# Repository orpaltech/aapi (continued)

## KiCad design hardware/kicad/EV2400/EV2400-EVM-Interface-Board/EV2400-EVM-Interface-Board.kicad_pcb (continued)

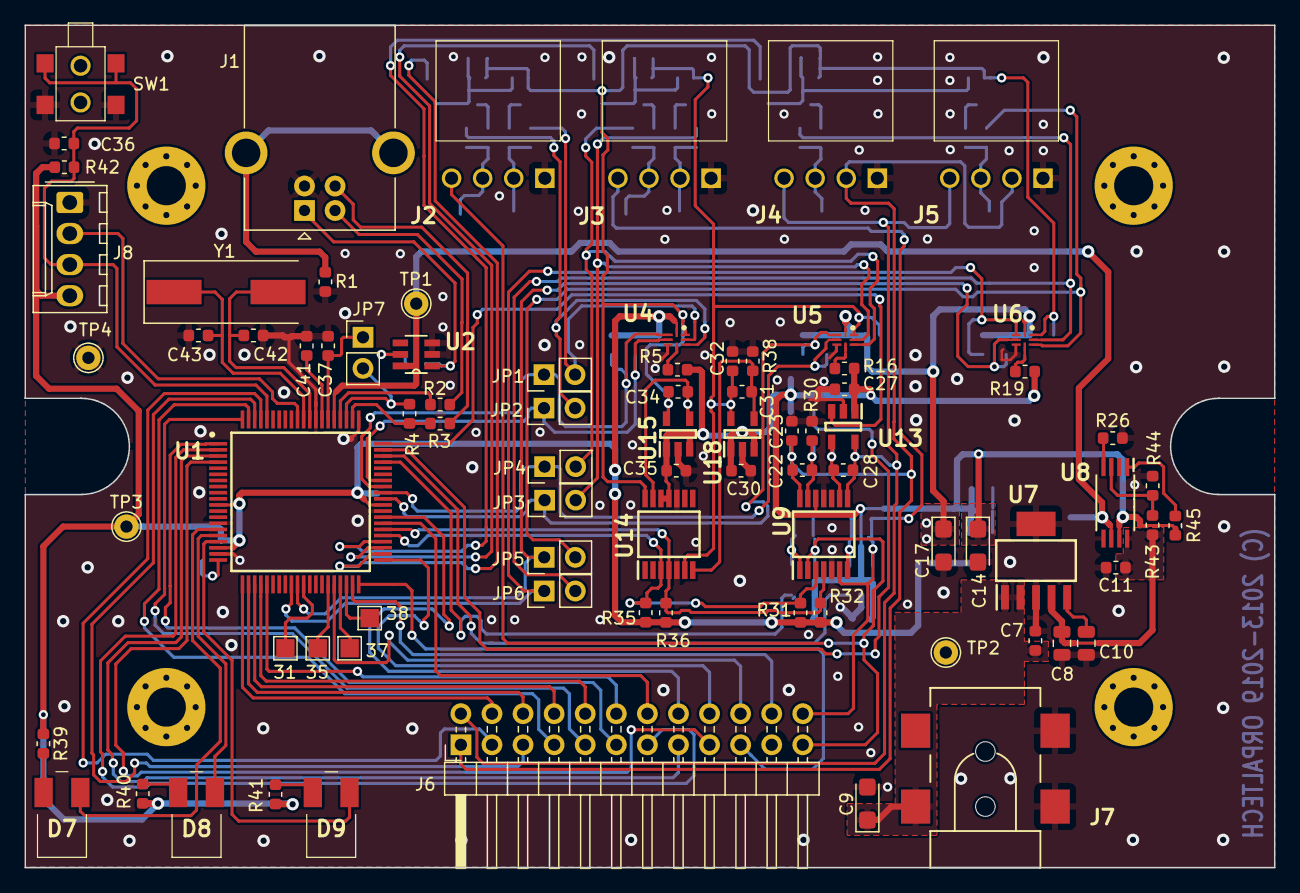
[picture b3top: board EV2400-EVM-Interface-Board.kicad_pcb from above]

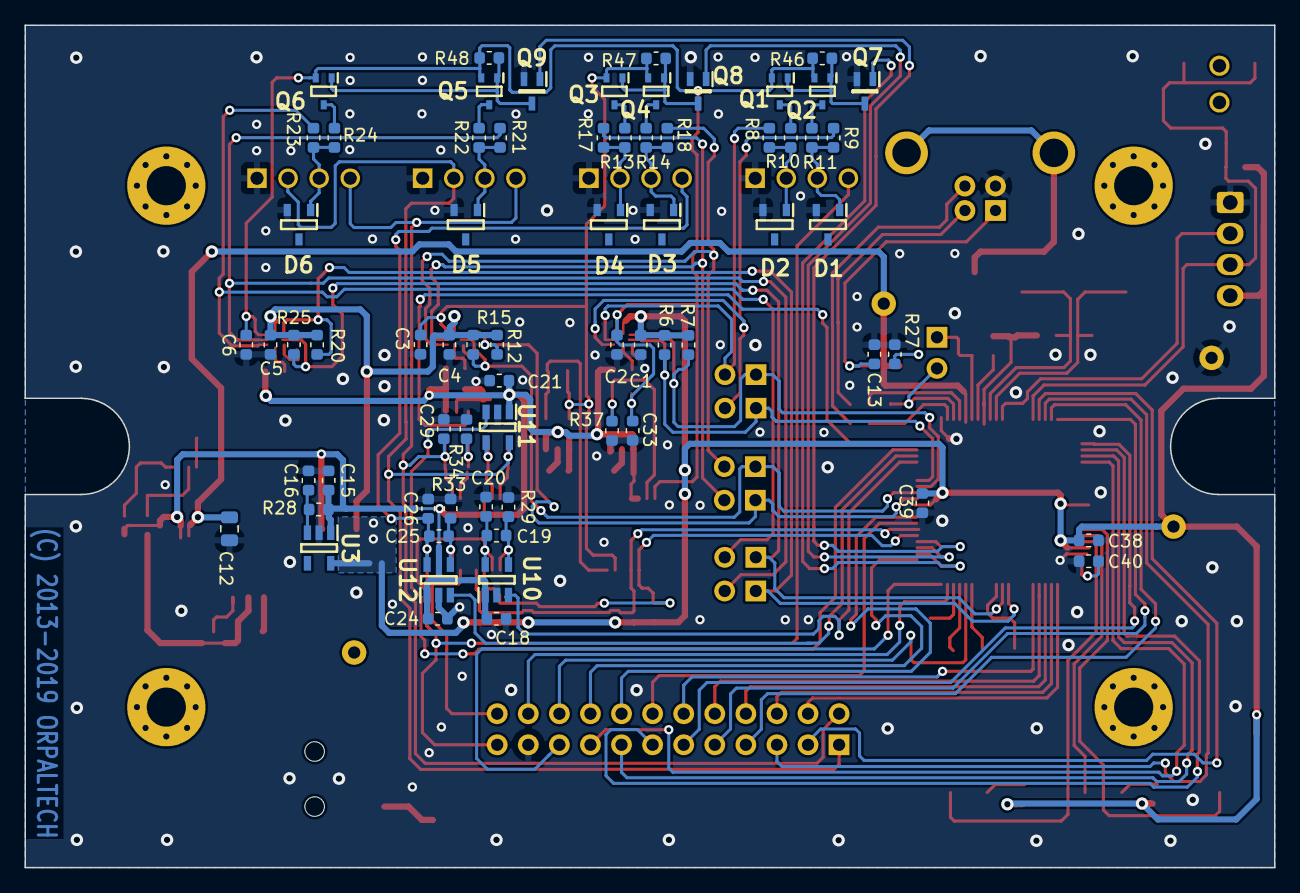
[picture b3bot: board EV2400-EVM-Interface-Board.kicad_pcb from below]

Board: 2 copper layers, 102.1 x 68.8 mm, 150 parts (68 on the bottom side), 106 nets.

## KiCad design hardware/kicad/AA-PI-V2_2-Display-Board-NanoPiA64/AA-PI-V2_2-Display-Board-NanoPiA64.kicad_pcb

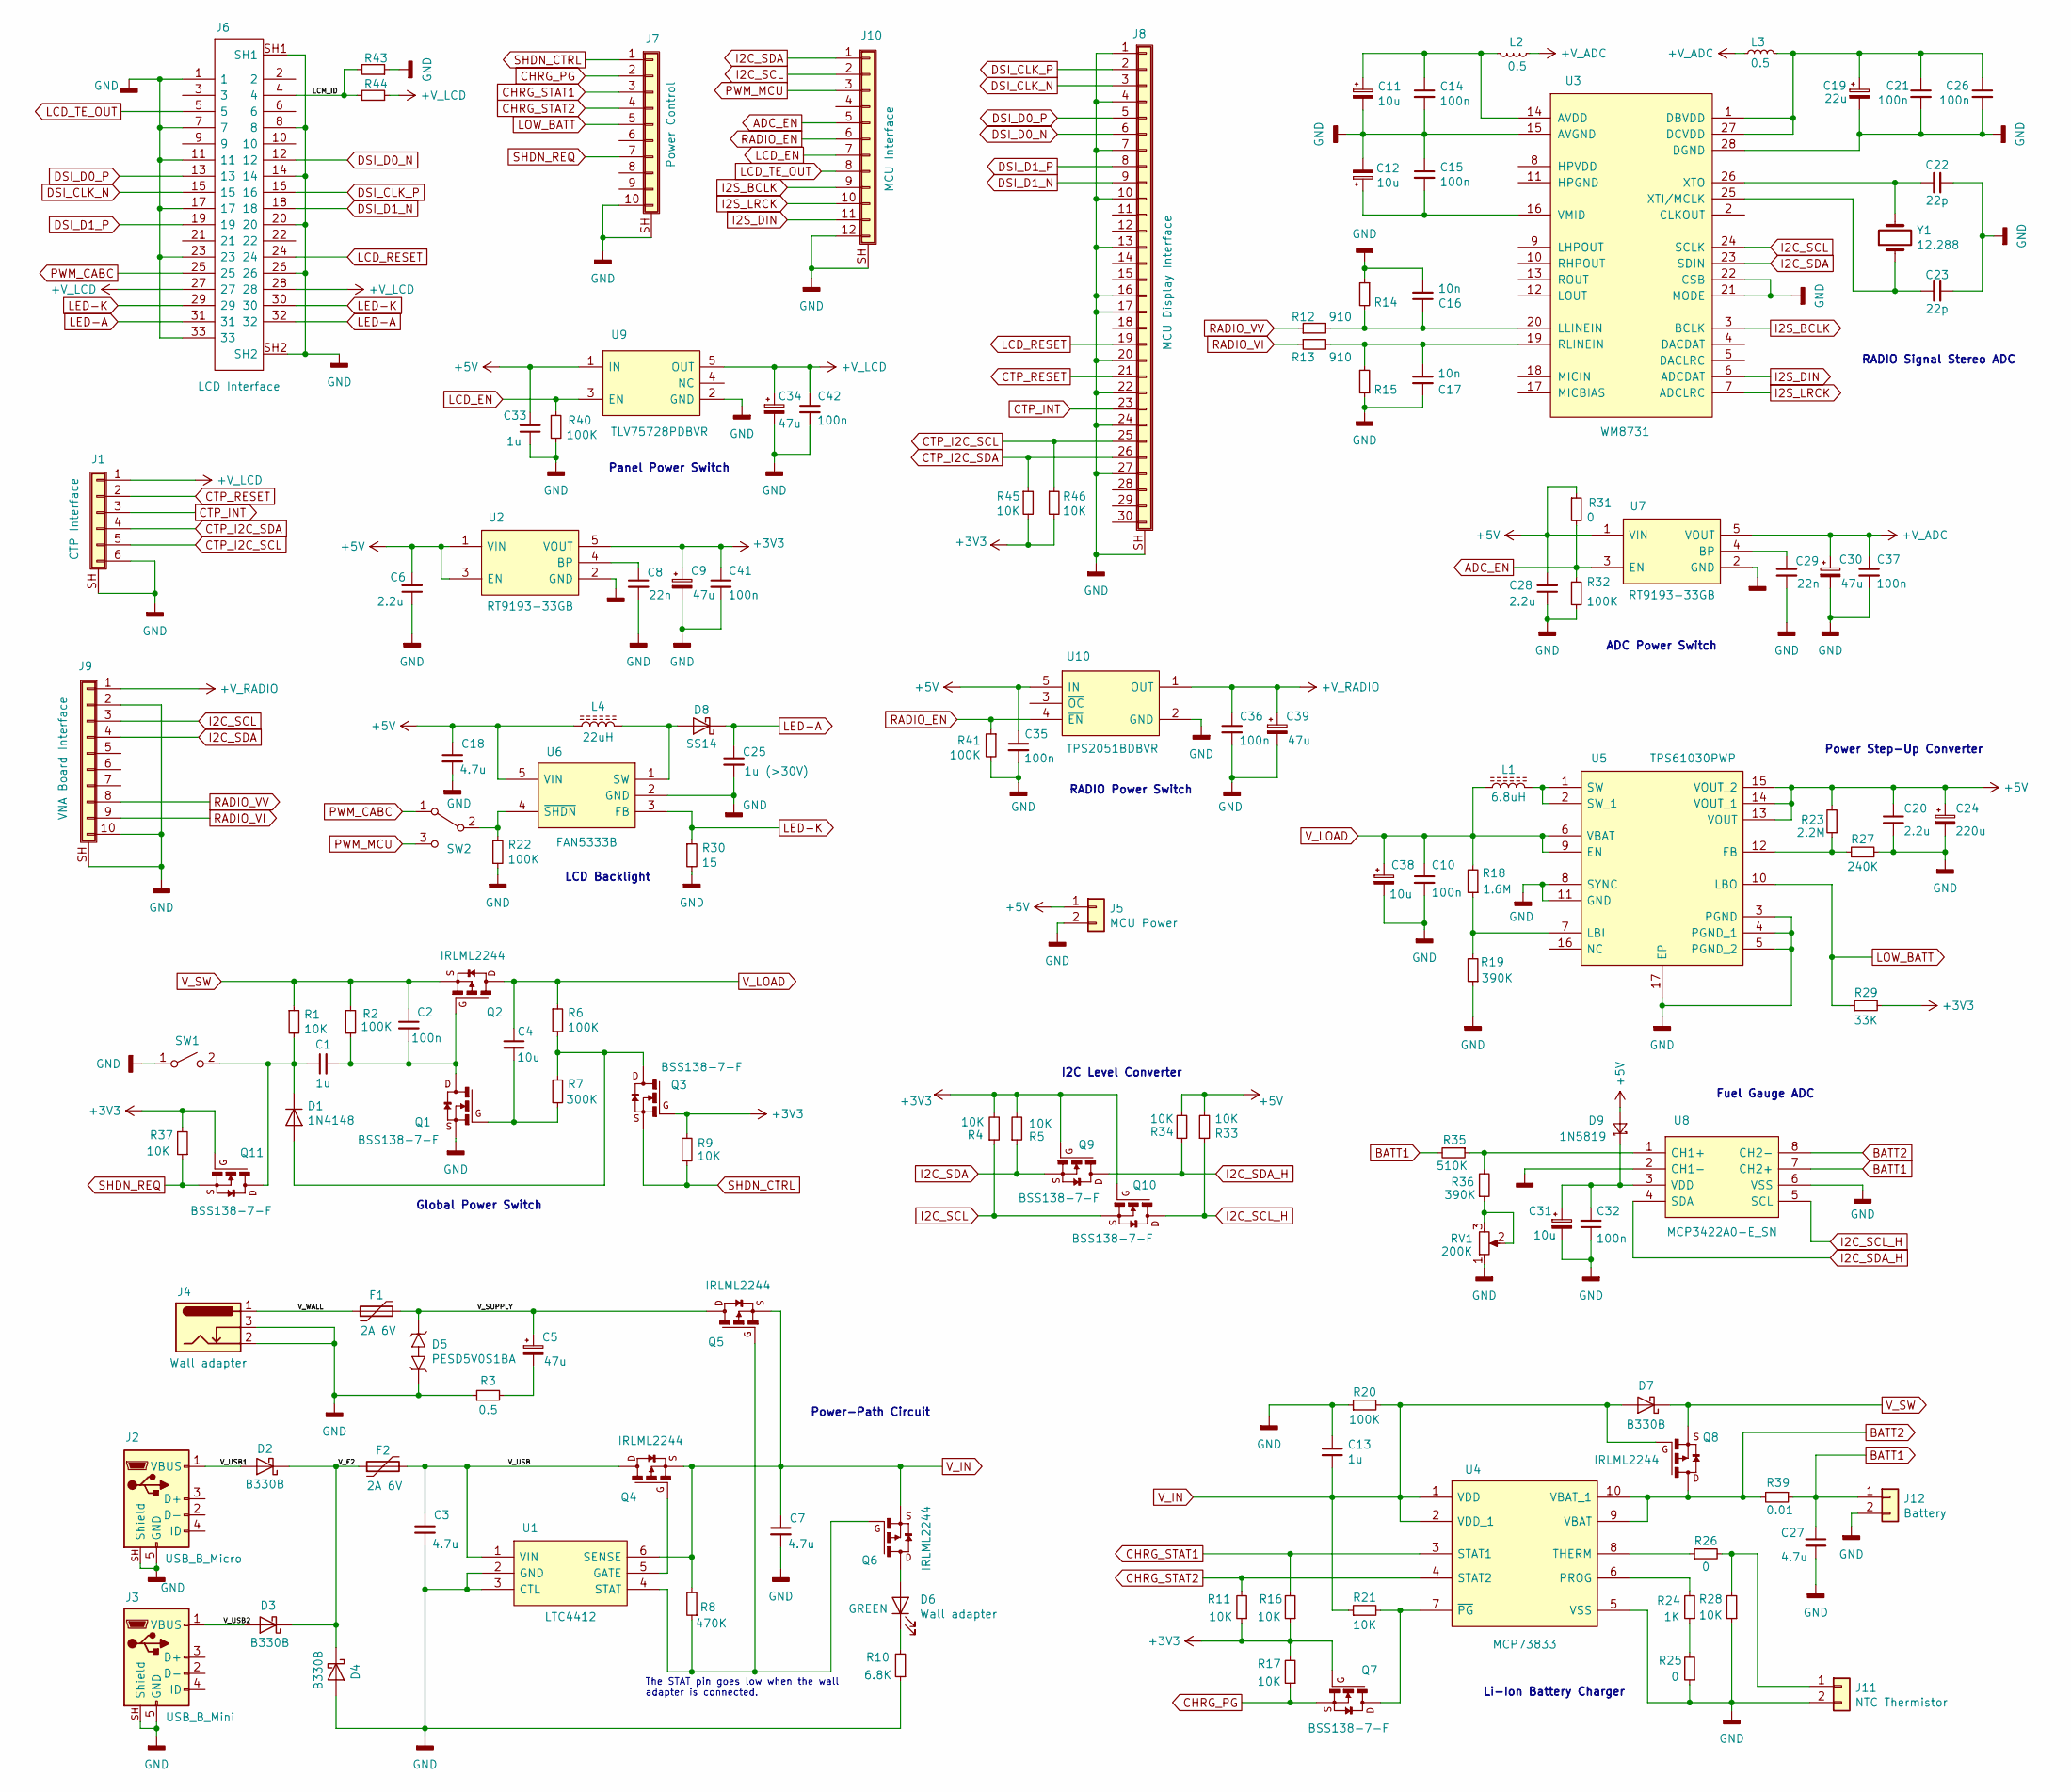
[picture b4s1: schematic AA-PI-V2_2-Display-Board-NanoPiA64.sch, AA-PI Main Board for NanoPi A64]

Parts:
C1, C33: 1u; C_0805_2012Metric_Pad1.15x1.40mm_HandSolder
C2, C10, C14, C15, C21, C26, C32, C35, C36, C37, C41, C42: 100n; C_0805_2012Metric_Pad1.15x1.40mm_HandSolder
C3, C7, C27: 4.7u; C_1206_3216Metric_Pad1.42x1.75mm_HandSolder
C4: 10u; C_0805_2012Metric_Pad1.15x1.40mm_HandSolder
C5, C9, C30, C34, C39: 47u; CP_EIA-3528-21_Kemet-B
C6, C28: 2.2u; C_0805_2012Metric_Pad1.15x1.40mm_HandSolder
C8, C29: 22n; C_0805_2012Metric_Pad1.15x1.40mm_HandSolder
C11, C12, C31: 10u; CP_EIA-3216-18_Kemet-A
C13: 1u; C_1206_3216Metric_Pad1.42x1.75mm_HandSolder
C16, C17: 10n; C_0805_2012Metric_Pad1.15x1.40mm_HandSolder
C18: 4.7u; C_0805_2012Metric_Pad1.15x1.40mm_HandSolder
C19: 22u; CP_EIA-3216-18_Kemet-A
C20: 2.2u; C_1206_3216Metric_Pad1.42x1.75mm_HandSolder
C22, C23: 22p; C_0805_2012Metric_Pad1.15x1.40mm_HandSolder
C24: 220u; CP_EIA-7343-31_Kemet-D
C25: 1u (>30V); C_1206_3216Metric_Pad1.42x1.75mm_HandSolder
C38: 10u; CP_EIA-3528-21_Kemet-B
D1: 1N4148; D_SOD-323_HandSoldering
D2, D3, D4, D7: B330B; D_SMB
D5: PESD5V0S1BA; D_SOD-323_HandSoldering
D6: Wall adapter; LED_0805_2012Metric_Pad1.15x1.40mm_HandSolder
D8: SS14; D_SMA
D9: 1N5819; D_SOD-323_HandSoldering
F1, F2: 2A 6V; Fuse_1206_3216Metric_Pad1.42x1.75mm_HandSolder
J1: CTP Interface; FPC-0.5-1-6P_Clamshell_Bottom
J2: USB_B_Micro; USB_Micro_B_Female_10118192
J3: USB_B_Mini; USB_Mini-B_Lumberg_2486_01_Horizontal
J4: Wall adapter; DC-050-SMD-Power-Jack
J5: MCU Power; JST_PH_B2B-PH-SM4-TB_1x02-1MP_P2.00mm_Vertical
J6: LCD Interface; FH26-33S-0.3SHW; Manufacturer_Part_Number FH26-33S-0.3SHW
J7: Power Control; 1.25-AB-SMT-10pin-Vertical
J8: MCU Display Interface; FPC-0.5-1-30P_Clamshell_Bottom
J9: VNA Board Interface; 1.25-AB-SMT-10pin-Vertical
J10: MCU Interface; 1.25-AB-SMT-12pin-Vertical
J11: NTC Thermistor; JST_PH_B2B-PH-SM4-TB_1x02-1MP_P2.00mm_Vertical
J12: Battery; JST_PH_B2B-PH-SM4-TB_1x02-1MP_P2.00mm_Vertical
L1: 6.8uH; CDRH124
L2, L3: 0.5; L_0805_2012Metric_Pad1.15x1.40mm_HandSolder
L4: 22uH; CD54
Q1, Q3, Q7, Q9, Q10, Q11: BSS138-7-F; SOT-23
Q2, Q4, Q5, Q6, Q8: IRLML2244; SOT-23
R1, R4, R5, R9, R11, R16, R17, R21, R28, R33, R34, R37, R45, R46: 10K; R_0805_2012Metric_Pad1.15x1.40mm_HandSolder
R2, R6, R20, R22, R32, R40, R41: 100K; R_0805_2012Metric_Pad1.15x1.40mm_HandSolder
R3: 0.5; R_0805_2012Metric_Pad1.15x1.40mm_HandSolder
R7: 300K; R_0805_2012Metric_Pad1.15x1.40mm_HandSolder
R8: 470K; R_0805_2012Metric_Pad1.15x1.40mm_HandSolder
R10: 6.8K; R_0805_2012Metric_Pad1.15x1.40mm_HandSolder
R12, R13: 910; R_0805_2012Metric_Pad1.15x1.40mm_HandSolder
R14, R15: void; R_0805_2012Metric_Pad1.15x1.40mm_HandSolder
R18: 1.6M; R_0805_2012Metric_Pad1.15x1.40mm_HandSolder
R19, R36: 390K; R_0805_2012Metric_Pad1.15x1.40mm_HandSolder
R23: 2.2M; R_0805_2012Metric_Pad1.15x1.40mm_HandSolder
R24: 1K; R_0805_2012Metric_Pad1.15x1.40mm_HandSolder
R25, R26, R31: 0; R_0805_2012Metric_Pad1.15x1.40mm_HandSolder
R27: 240K; R_0805_2012Metric_Pad1.15x1.40mm_HandSolder
R29: 33K; R_0805_2012Metric_Pad1.15x1.40mm_HandSolder
R30: 15; R_0805_2012Metric_Pad1.15x1.40mm_HandSolder
R35: 510K; R_0805_2012Metric_Pad1.15x1.40mm_HandSolder
R39: 0.01; R_0805_2012Metric_Pad1.15x1.40mm_HandSolder
R43, R44: 10K; R_0603_1608Metric_Pad1.05x0.95mm_HandSolder
RV1: 200K; SMD-Potentiometer-Trimmer-B6W-3x3T
SW1: SW_SPST; SW_SPST_CK_RS282G05A3
SW2: SW_SPDT; SW_SPDT_PCM12
U1: LTC4412; SOT95P280X100-6N; Manufacturer_Part_Number LTC4412ES6#TRMPBF
U2, U7: RT9193-33GB; SOT94P279X130-5N; Manufacturer_Part_Number RT9193
U3: WM8731; SOP65P780X200-28N; Manufacturer_Part_Number WM8731/L
U4: MCP73833; SOP50P490X110-10N; Manufacturer_Part_Number MCP73833-FCI/UN
U5: TPS61030PWP; SOP65P640X120-17N; Manufacturer_Part_Number TPS61030PWP
U6: FAN5333B; SOT95P270X145-5N; Manufacturer_Part_Number FAN5333BSX
U8: MCP3422A0-E_SN; SOIC127P600X175-8N; Manufacturer_Part_Number MCP3422A0-E/SN
U9: TLV75728PDBVR; SOT95P280X145-5N; Manufacturer_Part_Number TLV757P
U10: TPS2051BDBVR; SOT95P280X145-5N; Manufacturer_Part_Number TPS2051BDBVR
Y1: 12.288; Crystal_SMD_5032-2Pin_5.0x3.2mm

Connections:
+3V3: C9.1, C41.1, Q3.1 (G), Q7.1 (G), Q9.1 (G), Q10.1 (G), Q11.1 (G), R4.2, R5.2, R9.2, R11.1, R16.1, R17.2, R29.2, R37.2, R45.2, R46.2, U2.5 (VOUT)
+5V: C6.2, C18.1, C20.1, C24.1, C28.2, C33.2, C35.1, D9.2 (A), J5.1, L4.1, R23.2, R31.1, R33.2, R34.2, U2.1 (VIN), U2.3 (EN), U5.13 (VOUT), U5.14 (VOUT_1), U5.15 (VOUT_2), U6.5 (VIN), U7.1 (VIN), U9.1 (IN), U10.5 (IN)
+V_ADC: C30.1, C37.1, L2.1, L3.1, U7.5 (VOUT)
+V_LCD: C34.1, C42.1, J1.1, J6.27, J6.28, R44.1, U9.5 (OUT)
+V_RADIO: C36.1, C39.1, J9.1, U10.1 (OUT)
/LCM_ID: J6.4, R43.2, R44.2
/V_F2: D2.1 (K), D3.1 (K), D4.1 (K), F2.1
/V_SUPPLY: C5.1, D5.2, F1.2, Q5.3 (D)
/V_USB: C3.1, F2.2, Q4.3 (D), U1.1 (VIN)
/V_USB1: D2.2 (A), J2.1 (VBUS)
/V_USB2: D3.2 (A), J3.1 (VBUS)
/V_WALL: F1.1, J4.1
ADC_EN: J10.5, R31.2, R32.1, U7.3 (EN)
BATT1: C27.1, J12.1, R35.2, R39.1, U8.7 (CH2+)
BATT2: Q8.3 (D), R39.2, U4.9 (VBAT), U4.10 (VBAT_1), U8.8 (CH2-)
CHRG_PG: J7.2, Q7.2 (S), R17.1
CHRG_STAT1: J7.3, R16.2, U4.3 (STAT1)
CHRG_STAT2: J7.4, R11.2, U4.4 (STAT2)
CTP_I2C_SCL: J1.5, J8.25, R46.1
CTP_I2C_SDA: J1.4, J8.26, R45.1
CTP_INT: J1.3, J8.23
CTP_RESET: J1.2, J8.21
DSI_CLK_N: J6.15, J8.3
DSI_CLK_P: J6.16, J8.2
DSI_D0_N: J6.12, J8.6
DSI_D0_P: J6.13, J8.5
DSI_D1_N: J6.18, J8.9
DSI_D1_P: J6.19, J8.8
GND: C3.2, C6.1, C7.2, C8.2, C9.2, C10.2, C11.2, C12.2, C13.1, C14.2, C15.1, C16.2, C17.2, C18.2, C19.2, C20.2, C21.2, C22.2, C23.2, C24.2, C25.2, C26.2, C27.2, C28.1, C29.2, C30.2, C31.2, C32.1, C33.1, C34.2, C35.2, C36.2, C37.2, C38.2, C39.2, C41.2, C42.2, D4.2 (A), D5.1, J1.6, J1.SH (Shield), J2.5 (GND), J2.SH (Shield), J3.5 (GND), J3.SH (Shield), J4.2, J4.3, J5.2, J6.1, J6.7, J6.8, J6.11, J6.14, J6.17, J6.20, J6.23, J6.26, J6.33, J6.SH1, J6.SH2, J7.10, J7.SH (Shield), J8.1, J8.4, J8.7, J8.10, J8.13, J8.16, J8.17, J8.20, J8.22, J8.24, J8.27, J8.SH (Shield), J9.2, J9.10, J9.SH (Shield), J10.12, J10.SH (Shield), J11.2, J12.2, Q1.2 (S), R3.1, R10.1, R14.1, R15.1, R19.1, R20.1, R22.2, R25.1, R27.2, R28.1, R30.2, R32.2, R40.2, R41.2, R43.1, RV1.1, SW1.1 (A), U1.2 (GND), U1.3 (CTL), U2.2 (GND), U3.15 (AVGND), U3.21 (MODE), U3.22 (CSB), U3.28 (DGND), U4.5 (VSS), U5.3 (PGND), U5.4 (PGND_1), U5.5 (PGND_2), U5.8 (SYNC), U5.11 (GND), U5.17 (EP), U6.2 (GND), U7.2 (GND), U8.2 (CH1-), U8.6 (VSS), U9.2 (GND), U10.2 (GND)
I2C_SCL: J9.3, J10.2, Q10.2 (S), R4.1, U3.24 (SCLK)
I2C_SCL_H: Q10.3 (D), R33.1, U8.5 (SCL)
I2C_SDA: J9.4, J10.1, Q9.2 (S), R5.1, U3.23 (SDIN)
I2C_SDA_H: Q9.3 (D), R34.1, U8.4 (SDA)
I2S_BCLK: J10.9, U3.3 (BCLK)
I2S_DIN: J10.11, U3.6 (ADCDAT)
I2S_LRCK: J10.10, U3.7 (ADCLRC)
LCD_EN: J10.7, R40.1, U9.3 (EN)
LCD_RESET: J6.24, J8.19
LCD_TE_OUT: J6.5, J10.8
LED-A: C25.1, D8.1 (K), J6.31, J6.32
LED-K: J6.29, J6.30, R30.1, U6.3 (FB)
LOW_BATT: J7.5, R29.1, U5.10 (LBO)
unnamed: C1.1, D1.1 (K), Q11.3 (D), R1.2, SW1.2 (B)
unnamed: C1.2, C2.2, Q1.3 (D), Q2.1 (G), R2.2
unnamed: C4.2, Q1.1 (G), R7.2
unnamed: C5.2, R3.2
unnamed: C8.1, U2.4 (BP)
unnamed: C11.1, C14.1, L2.2, U3.14 (AVDD)
unnamed: C12.1, C15.2, U3.16 (VMID)
unnamed: C16.1, R12.2, R14.2, U3.20 (LLINEIN)
unnamed: C17.1, R13.2, R15.2, U3.19 (RLINEIN)
unnamed: C19.1, C21.1, C26.1, L3.2, U3.1 (DBVDD), U3.27 (DCVDD)
unnamed: C22.1, U3.26 (XTO), Y1.2
unnamed: C23.1, U3.25 (XTI/MCLK), Y1.1
unnamed: C29.1, U7.4 (BP)
unnamed: C31.1, C32.2, D9.1 (K), U8.3 (VDD)
unnamed: D1.2 (A), Q3.3 (D), R6.2, R7.1
unnamed: D6.1 (K), R10.2
unnamed: D6.2 (A), Q6.3 (D)
unnamed: D8.2 (A), L4.2, U6.1 (SW)
unnamed: J11.1, R26.2, R28.2
unnamed: L1.2, U5.1 (SW), U5.2 (SW_1)
unnamed: Q4.1 (G), U1.5 (GATE)
unnamed: Q5.1 (G), Q6.1 (G), R8.1, U1.4 (STAT)
unnamed: Q7.3 (D), R21.2, U4.7 (~PG)
unnamed: R18.1, R19.2, U5.7 (LBI)
unnamed: R22.1, SW2.2 (B), U6.4 (~SHDN)
unnamed: R23.1, R27.1, U5.12 (FB)
unnamed: R24.1, R25.2
unnamed: R24.2, U4.6 (PROG)
unnamed: R26.1, U4.8 (THERM)
unnamed: R35.1, R36.2, U8.1 (CH1+)
unnamed: R36.1, RV1.2, RV1.3
PWM_CABC: J6.25, SW2.1 (A)
PWM_MCU: J10.3, SW2.3 (C)
RADIO_EN: J10.6, R41.1, U10.4 (~EN)
RADIO_VI: J9.9, R13.1
RADIO_VV: J9.8, R12.1
SHDN_CTRL: J7.1, Q3.2 (S), R9.1
SHDN_REQ: J7.7, Q11.2 (S), R37.1
V_IN: C7.1, C13.2, D7.2 (A), Q4.2 (S), Q5.2 (S), Q6.2 (S), Q8.1 (G), R8.2, R20.2, R21.1, U1.6 (SENSE), U4.1 (VDD), U4.2 (VDD_1)
V_LOAD: C4.1, C10.1, C38.1, L1.1, Q2.3 (D), R6.1, R18.2, U5.6 (VBAT), U5.9 (EN)
V_SW: C2.1, D7.1 (K), Q2.2 (S), Q8.2 (S), R1.1, R2.1

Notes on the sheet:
The STAT pin goes low when the wall adapter is connected.
I2C Level Converter
Fuel Gauge ADC
Li-Ion Battery Charger
Global Power Switch
LCD Backlight
Panel Power Switch
RADIO Power Switch
RADIO Signal Stereo ADC
ADC Power Switch
Power Step-Up Converter
Power-Path Circuit

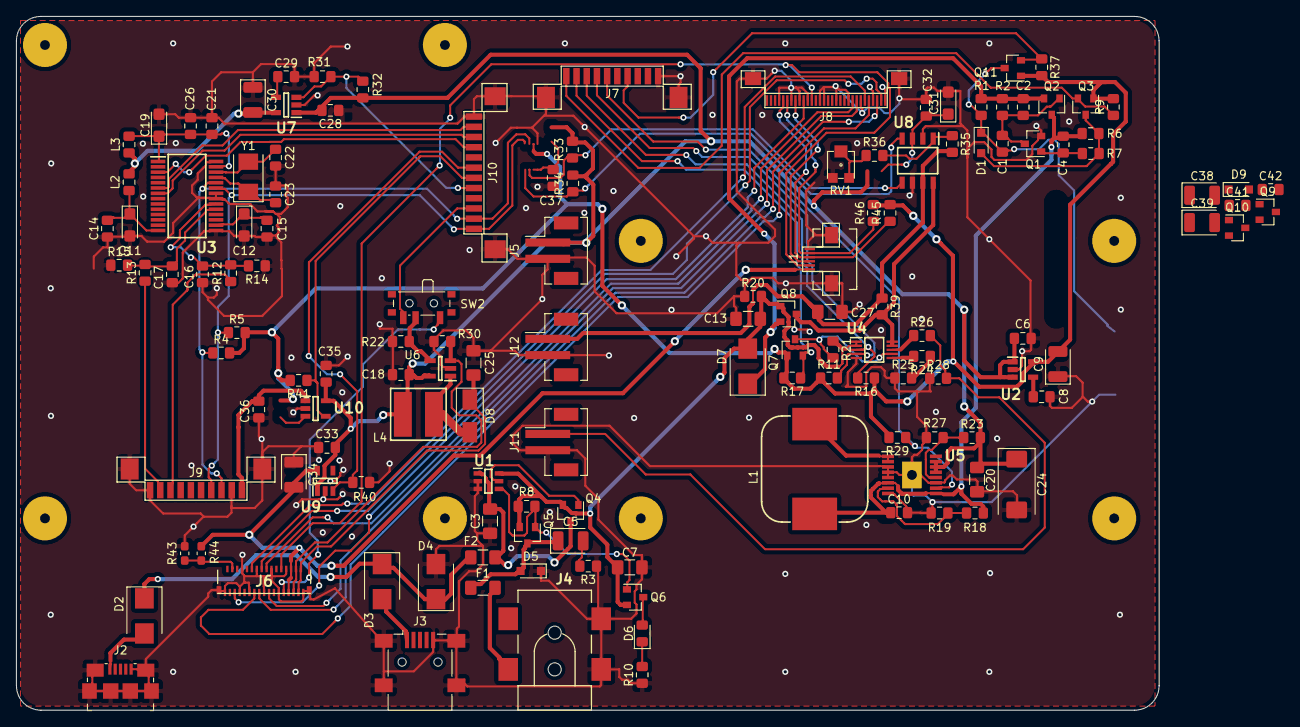
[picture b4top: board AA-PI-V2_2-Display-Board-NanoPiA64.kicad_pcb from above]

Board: 2 copper layers, 140.0 x 85.0 mm, 147 parts (1 on the bottom side), 83 nets.

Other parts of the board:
CH1: CTP-CABLE-HOLE
HOLE2: LCD-0.3-33P-CABLE-HOLE
SS1, SS2, SS3, SS4, SS5, SS6, SS7, SS8: PCB-Standoff-Spacer-SMD-M3

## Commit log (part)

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2018-10-13 initial
2018-10-13 add hardware
2018-10-13 remove useless files
2018-10-13 remove eagle import
2018-11-03 kicad projects update
2018-11-03 rename folder
2018-11-04 Rotated DSI connector to match RPI orientation
2018-11-04 Encreased thickness of the antenna route
2018-11-30 planned update (sources)
2018-11-30 planned update (hardware)
2018-12-05 Display board for NanoPiA64
2018-12-05 cleanup
2018-12-20 some docs
2019-02-23 hardware: kicad schematics
2019-03-03 panel datasheet
2019-03-04 pdf schematic for NanoPi A64 v2.2
2019-08-19 Planned update
2019-08-19 Removed obsolete schematics
2019-08-19 Add radio board
2019-08-26 readme updates
2019-09-27 Add EV2400 interface
2019-09-27 removed old AA-PI kicad sources
2019-10-01 EV2400 PCB update
2019-11-16 Updates: EV2400 kicad sources
2020-02-05 EV2400: remove gerber files
2025-03-11 Update kikad files
2025-09-09 Update EV2400 kicad files
2025-09-09 Remove garbage files
2025-12-10 Updated to v4.3
2026-02-07 Add EV2400-clone images
2026-02-07 Some code cleanup in antenna-analyzer project
2026-02-28 Add images for v4.2
2026-03-18 Add docs & readme for bq34z100-g1 setup
2026-03-18 Update battery readme
2026-03-19 Add notes about dynamic rebound into the battery README
2026-05-20 Continue working on smith chart
2026-06-29 Planned updates: radio part, UI
2026-06-29 Planned updates: radio board design files
2026-06-29 Planned updates: display board design files
